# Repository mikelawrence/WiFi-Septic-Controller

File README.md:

# Wireless Septic Controller
I had some problems with my newly installed aerobic septic system when hurricane Harvey blew through. There was no significant flooding but there was plenty of rain and that seemed to cause the system to override pump multiple times. This board is designed to give visibility as to how often the pump runs and will detail alarm conditions. The effluent pump is controlled with an external 50A Solid-State-Relay (SSR). This board also provides an alarm output required by most aerobic septic systems. Normally the alarm switches are wired in parallel so that any alarm condition will turn on the light and audible alert. This board has separate inputs for three alarm switches so that the alarm condition can be identified. This board supports the following alarm types: air pressure failure alarm, tank high level alarm, and bleach low level alarm. WiFi is provided by an ATWINC1500 module which is an excellent low power WiFi module that is directly supported by Arduino. This board is fully compatible with the Arduino MRK1000 which includes a SAMD21G18 ARM processor and a ATWINC1500 module. This board uses MQTT to communicate with Home Assistant home automation software. The MQTT client/server model is very effective in this situation.

This PCB design uses my custom libraries available here [Mike's KiCad Libraries](https://github.com/mikelawrence/KiCad-Libraries).

This PCB was designed with [KiCad 5.1.2](http://kicad.org).

_Note: There is dangerous voltage present on this PCB. Use care when handling this board. Housing this board in a box is required to protect users from electrocution._

_Note: The LMZ21700 Simple Switcher, SAMD21G18 ARM Processor, and ATWINC1500 WiFi Module have exposed pads on the bottom which requires either a reflow oven or hot air to solder properly._

For Bill of Materials generation I use my version of [KiBoM](https://github.com/mikelawrence/KiBoM) forked from [SchrodingersGat](https://github.com/SchrodingersGat/KiBoM).

## Status
* Rev 1.1 PCB has been updated to support KiCad 5.1 libraries. Some footprints changed when libraries were updated but changes were minimal. This board has NOT been tested.
  * Order the PCB from [OSH Park](https://oshpark.com/shared_projects/a805S6zq).
  * Order the parts from Mouser using this [Shared BOM](https://www.mouser.com/ProjectManager/ProjectDetail.aspx?AccessID=a71ed4612f).
* Rev 1.0 PCB has been ordered, assembled, and tested. Hardware is fully operational.
  * Order the PCB from [OSH Park](https://oshpark.com/shared_projects/bguWSc9J).
  * Order the parts from Mouser using this [Shared BOM](https://www.mouser.com/ProjectManager/ProjectDetail.aspx?AccessID=a71ed4612f).

## Board Preview

## Design
### Input Power
A transformer converts the 115VAC to 10VAC through a standard bridge rectifier and capacitor filter to arrive at approximately 12VDC. This voltage is fed to both a 3.3VDC and 5VDC Simpler Switcher from Texas Instruments (LMZ21700). The switchers can also be fed by the 5VDC from the USB connector when the 115VAC is not connected. But make note, the 5VDC is no longer regulated.

### Alarm Contact Inputs
There are three alarm contact inputs: air pressure failure alarm, tank high level alarm, and bleach low level alarm. Aerobic septic systems have an air compressor that pumps air into the septic tank, hence the name "aerobic". This air pump promotes bacterial growth and it runs all the time. If the air pump stops producing air pressure the air pressure failure alarm contact closes. Many aerobic septic systems use liquid bleach for the chlorine source and some regulatory boards require a low bleach level alarm. My aerobic septic system has three float switches but only one is the tank high level alarm. This float switch is at the highest point in the tank and this alarm means the pump cannot keep up with the water entering the tank. This is usually caused by the effluent pump failing.

In the previous wiring of the septic controller the alarm contacts were wired in parallel logically "or'ing" the alarms. The contacts switched 115VAC to the alarm light and audible alert. In order to determine the actual alarm state the wiring was changed to directly connect these contacts to the the board and they no longer switch 115VAC. The alarm contact inputs use a simple pullup to 5VDC and a Schmidt Trigger Inverter (SN74LVC2G14). Note: software debounce is still required. A high value pullup resistor and series resistor (both 100k) were selected to reduce current levels when accidental high voltages are applied to the input. ESD Protection devices are included to further protect the inputs. Due the inverted nature of the SN74LVC2G14 the software sees a logic high when the contact is closed.

### Sense Inputs
There are two 115VAC sense inputs (S1 and S2). These inputs are connected to an On Semiconductor MID400 AC Line Monitor. This optically-isolated device provides a logic low when 115VAC is present on the input. There is no flickering due to 60Hz AC. S1 is used to sense when the effluent pump has power. These is needed because the effluent pump can be turned on when the override float is tripped. S2 is currently unused.

### Relay Outputs
There are two relay outputs on the PR and ALM. Both are switched 115VAC by small board mount solid state relays  (). These SSRs provide overload protection for both temperature and current. The Pump Relay (PR) output is connected to the effluent pump 50A solid state relay (Crydom CWA2450-10). A 50A relay is needed to drive the 3/4hp effluent pump. Note this relay is controlled by 115VAC. The other relay output (AL) is the alarm output. The alarm light and audible alert require 10W at 115VAC. The alarm output is switched on when any alarm contact is closed. There is no software intervention required to produce an alarm.

### SAMD ARM Processor and WiFi Module
The ARM processor and ATWINC1500 WiFi module are wired identical to the MKR1000 Arduino board, thus the Arduino development environment is used for software development and the ATWINC1500 module is directly supported. Digital power is 3.3V and while the LCD is 5V there are no 5V outputs driving 3.3V inputs on the ARM processor so there is no problem wiring the LCD directly to the ARM processor. The LCD recognizes anything above 2.2VDC as a high so 3.3VDC logic outputs from ARM processor will be correctly interpreted by the LCD.

## Setup
### Arduino Setup
This board is designed to mimic a [MKR1000](https://store.arduino.cc/usa/arduino-mkr1000) board from Arduino. Make sure the the MKR1000 board is supported by installing Arduino SAMD Boards package. Do this by opening the Board Manager as shown below.

Type in "samd" in the filter edit and you will see several options. Select "Arduino SAMD Boards (32-bits ARM Cortex-M0+)" and install the latest version as shown below.

It will take a few minutes to download and install the board package. Once complete it's time to install the necessary libraries. Start by opening the Library Manager as shown below.

Type in "mqtt" in the filter edit and scroll down until you see "MQTT by Joel Gaehwiler" as shown below.

Once "MQTT" is installed repeat the install for the following libraries.

* WiFi101 by Arduino
* WiFiOTA by Arduino
* OneWire by Paul Stoffregen and many others
* DallasTemperature by Miles Burton and others

### Board Setup
The Arduino development environment expects a bootloader in the SAMD ARM processor which will allow programming via USB. The bootloader must be programmed first using a supported programming pod. I used an "Atmel-ICE" pod but there are other options. First make sure you have selected the "Arduino/Genuino MKR1000" board as shown below.

Next select your programmer.

Make sure the board is powered via USB and the programmer is connected to the debug connector then select "Burn Bootloader".

Now the bootloader is programmed it's time to load the "WiFi101 FirmwareUpdater" example. This will update the firmware in the ATWINC1500 module.

Now "Upload" the "WiFi101 FirmwareUpdater" example.

Update the ATWINC1500 module by selecting "WiFi101 Firmware Updater".

Click the "Update Firmware" button.

Finally open the "Septic_WiFi_Controller.ino" sketch downloaded from GitHub. Update the necessary defines for your Wireless network and MQTT server settings see the [Code README](code/README.md) for more information. Now upload it just like the "WiFi101 FirmwareUpdater" example. All done!

# Acknowledgments
[Arduino](www.arduino.cc) kindly develops open source hardware and software which makes writing software for the board incredibly easy.

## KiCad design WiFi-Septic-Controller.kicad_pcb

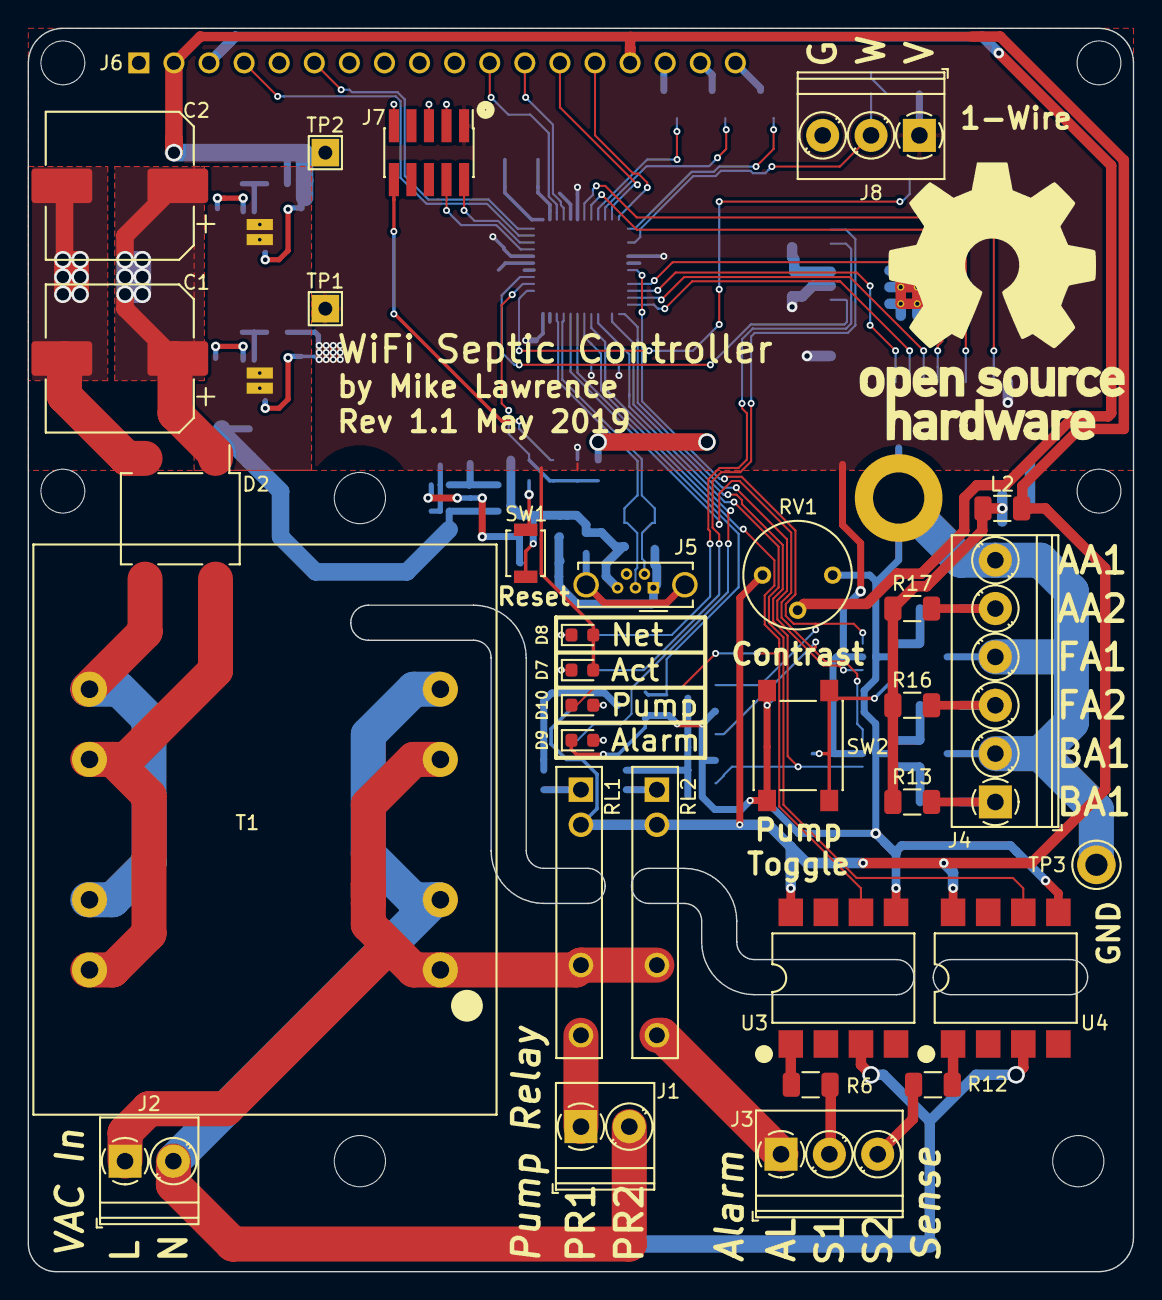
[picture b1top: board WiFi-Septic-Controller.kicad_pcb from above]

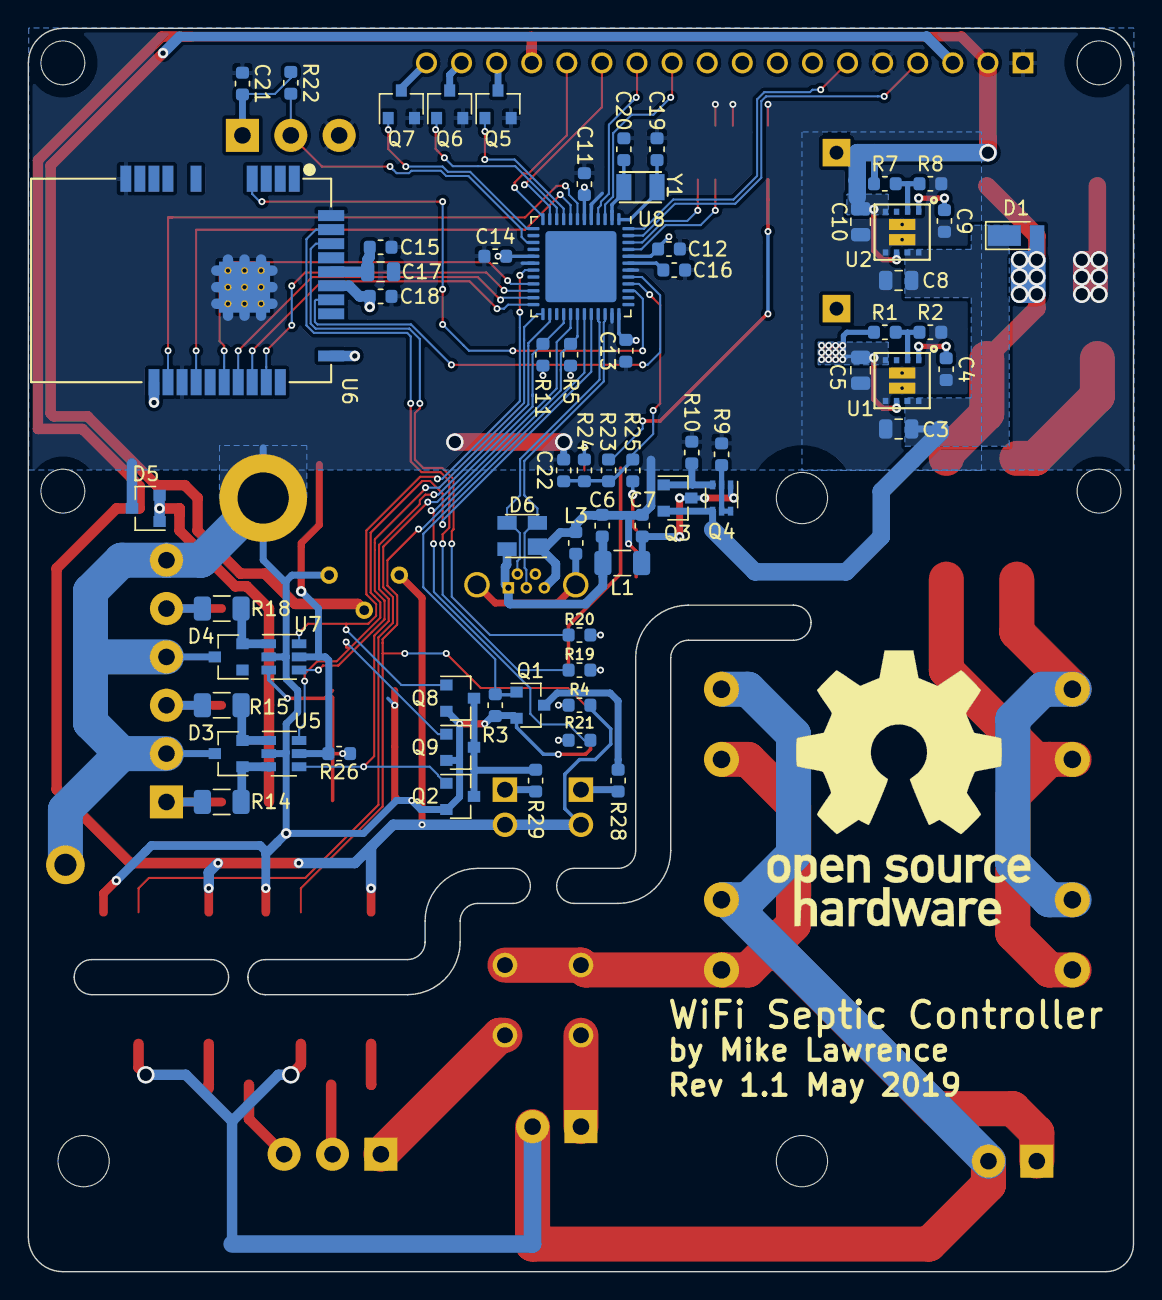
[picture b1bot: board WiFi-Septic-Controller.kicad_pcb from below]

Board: 2 copper layers, 80.0 x 90.0 mm, 102 parts (66 on the bottom side), 83 nets.

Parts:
C1, C2: 330uF; CP_Elec_10x10.5
C3, C5, C8, C10, C17: 22uF; C_0805_2012Metric
C4, C9: 3300pF; C_0603_1608Metric
C6, C7: 1000pF; C_0603_1608Metric
C11, C12, C13, C14, C15, C21, C22: 0.1uF; C_0603_1608Metric
C16, C18: 1uF; C_0603_1608Metric
C19, C20: 15pF; C_0603_1608Metric
D1: DFLS130; D_PowerDI-123
D2: D_Bridge_+-AA; Diode_Bridge_Vishay_DFS
D3, D4, D5: TPD2E2U06; SOT-23
D6: PRTR5V0U2X; SOT-143
D7: Yellow; LED_0603_1608Metric
D8: Green; LED_0603_1608Metric
D9: Red; LED_0603_1608Metric
D10: Blue; LED_0603_1608Metric
J1, J2: Screw_Terminal_01x02; TerminalBlock_Phoenix_PT-1,5-2-3.5-H_1x02_P3.50mm_Horizontal
J3, J8: Screw_Terminal_01x03; TerminalBlock_Phoenix_PT-1,5-3-3.5-H_1x03_P3.50mm_Horizontal
J4: Screw_Terminal_01x06; TerminalBlock_Phoenix_PT-1,5-6-3.5-H_1x06_P3.50mm_Horizontal
J5: USB_B_Micro; USB_Micro-B_Wuerth_614105150721_Vertical_CircularHoles
J6: GWT-C1627A-RGB
J7: Cortex Debug; PinHeader_2x05_P1.27mm_Vertical_SMD
L1, L2: 1k@100MHz; L_1206_3216Metric
L3: 470@100MHz; L_0603_1608Metric
MK1: Mounting_Hole_PAD; 6-32_PTH_Mounting_Hole
MK2, MK3, MK4: 6-32_NPTH_Mounting_Hole
Q1, Q2, Q5, Q6, Q7, Q8, Q9: 2N7002; SOT-23
Q3: DMG2305UX; SOT-23
Q4: BCM857BS; SOT-363_SC-70-6
R1: 1.21M; R_0603_1608Metric
R2: 383k; R_0603_1608Metric
R3, R5, R9, R11, R24, R26: 10k; R_0603_1608Metric
R4: 169R; R_0603_1608Metric
R6, R12, R13, R14, R15, R16, R17, R18: 22k; R_1206_3216Metric
R7: 232k; R_0603_1608Metric
R8: 44.2k; R_0603_1608Metric
R10: 47k; R_0603_1608Metric
R19, R20, R21: 130R; R_0603_1608Metric
R22: 4.7k; R_0603_1608Metric
R23: 39R; R_0603_1608Metric
R25: 330R; R_0603_1608Metric
R28, R29: 698R; R_0603_1608Metric
RL1, RL2: CPC1511Y; Relay_IXYS_PowerSIP
RV1: 10k; Potentiometer_Bourns_3339P_Vertical
SW1: Reset; SW_SPST_B3U-1000P
SW2: Pump; SW_SPST_PTS645
T1: VPP-XFMR; Triad_VPP_5.0VA
TP1: 3.3V; TestPoint_THTPad_2.0x2.0mm_Drill1.0mm
TP2: 5V; TestPoint_THTPad_2.0x2.0mm_Drill1.0mm
TP3: GND; TestPoint_Keystone_5010-5014_Multipurpose
U1, U2: LMZ21700; Converter_DCDC_Texas-SIL0008E
U3, U4: MID400; SMDIP-8_W9.53mm
U5, U7: 74LVC2G14; SOT-23-6
U6: ATWINC1500-MR210UB; Microchip_ATWINC1500-MR210UB
U8: SAMD21G18-M; QFN-48-1EP_7x7mm_P0.5mm_EP5.15x5.15mm
Y1: 32.768kHz; Crystal_SMD_Abracon_ABS07-2Pin_3.2x1.5mm

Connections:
+3V3: C5.1, C11.2, C12.2, C13.2, C14.2, C18.2, C21.2, D7.2, D8.2, J7.1, J8.1, R1.1, R5.2, R11.2, R22.1, R24.2, R26.1, TP1.1, U1.4, U1.6, U5.5, U6.10, U6.20, U6.23, U7.5, U8.6, U8.17, U8.36, U8.44
+5V: C10.1, J6.2, J6.15, L2.1, R4.2, R7.1, RL1.2, RL2.2, RV1.3, TP2.1, U2.4, U2.6, U3.8, U4.8
+12V: C1.1, C2.1, D1.2, D2.1
/A0: J6.11, U8.3
/A1: J6.4, U8.47
/A2: J6.6, U8.48
/A3: Q5.1, U8.9
/A4: Q6.1, U8.10
/A5: J6.13, U8.11
/A6: J6.14, U8.12
/ALM: J3.1, RL2.4
/AREF: J6.12, U8.4
/D0: Q1.1, R3.1, U8.31
/D1: Q9.1, U5.6, U8.32
/D2: J8.2, R22.2, U8.15
/D4: Q8.1, U7.6, U8.19
/D6: R21.1, U8.29
/D7: D10.1, R5.1, U3.6, U8.30
/MISO: R11.1, U4.6, U8.28
/MOSI: U7.4, U8.25
/P1: J3.2, R6.1
/P2: J3.3, R12.1
/PR1: J1.1, RL1.4
/SCK: Q2.1, U5.4, U8.26
/SDA: Q7.1, U8.13
/SWCLK: J7.4, U8.45
/SWDIO: J7.2, U8.46
/USB_N: D6.3, J5.2, U8.33
/USB_P: D6.2, J5.3, U8.34
/VSUPPLY: C3.1, C8.1, D1.1, Q3.2, Q4.4, U1.7, U1.8, U2.7, U2.8
/WINC_EN: U6.22, U8.41
/WINC_MISO: U6.17, U8.24
/WINC_MOSI: U6.15, U8.21
/WINC_SCK: U6.18, U8.22
/WINC_WAKE: U6.11, U8.7
/~RESET~: C22.2, R23.1, R24.1, R25.1, U8.40
/~WINC_IRQ: U6.13, U8.8
/~WINC_RST: U6.4, U8.39
/~WINC_SS: U6.16, U8.23
GND: C1.2, C2.2, C3.2, C4.2, C5.2, C6.1, C7.1, C8.2, C9.2, C10.2, C11.1, C12.1, C13.1, C14.1, C15.1, C16.1, C17.2, C18.1, C19.1, C20.1, C21.1, C22.1, D2.2, D3.3, D4.3, D5.3, D6.1, D9.1, J4.2, J4.4, J4.6, J5.5, J6.1, J6.5, J7.3, J7.5, J7.9, J8.3, L3.1, MK1.1, Q1.2, Q2.2, Q5.2, Q6.2, Q7.2, Q8.2, Q9.2, R2.2, R3.2, R8.2, R9.2, R10.2, RV1.1, SW1.2, SW2.2, TP3.1, U1.5, U1.9, U1.10, U2.5, U2.9, U2.10, U3.5, U4.5, U5.2, U6.9, U6.12, U6.28, U6.29, U7.2, U8.5, U8.18, U8.35, U8.42
LINE: J2.1, RL1.3, RL2.3, T1.1, T1.4
NEUT: J1.2, J2.2, T1.3, T1.6, U3.3, U4.3
unnamed: C4.1, U1.1
unnamed: C7.2, L1.2, Q3.3, Q4.1
unnamed: C9.1, U2.1
unnamed: C15.2, C17.1, U6.24
unnamed: C16.2, U8.43
unnamed: C19.2, U8.1, Y1.1
unnamed: C20.2, U8.2, Y1.2
unnamed: D2.3, T1.9, T1.12
unnamed: D2.4, T1.7, T1.10
unnamed: D3.1, R14.2, U5.3
unnamed: D3.2, R15.2, U5.1
unnamed: D4.2, R18.2, U7.1
unnamed: D5.1, D5.2, L2.2, R13.1, R16.1, R17.1
unnamed: D7.1, R19.2
unnamed: D8.1, R20.2
unnamed: D9.2, R21.2
unnamed: D10.2, R4.1
unnamed: J4.1, R13.2, R14.1
unnamed: J4.3, R15.1, R16.2
unnamed: J4.5, R17.2, R18.1
unnamed: J5.6, L3.2
unnamed: J6.3, RV1.2
unnamed: J6.16, Q5.3
unnamed: J6.17, Q6.3
unnamed: J6.18, Q7.3
unnamed: J7.10, R23.2
unnamed: Q1.3, R28.1
unnamed: Q2.3, Q8.3, Q9.3, R29.1
unnamed: Q3.1, Q4.3, R10.1
unnamed: Q4.2, Q4.5, Q4.6, R9.1
unnamed: R1.2, R2.1, U1.2
unnamed: R6.2, U3.1
unnamed: R7.2, R8.1, U2.2
unnamed: R12.2, U4.1
unnamed: R19.1, U6.27
unnamed: R20.1, U6.26
unnamed: R25.2, SW1.1
unnamed: R26.2, SW2.1, U7.3
unnamed: R28.2, RL1.1
unnamed: R29.2, RL2.1
VBUS: C6.2, D6.4, J5.1, L1.1

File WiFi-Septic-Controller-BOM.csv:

Quantity,References,Description,Manufacturer,Part Number,Vendor,Vendor Part Number
2,C1 C2,"CAP, SMD 10X10.5, 20%, EC, 50V",Panasonic,EEE-FT1H331GP,Mouser,667-EEE-FT1H331GP
5,C3 C5 C8 C10 C17,"CAP, 0805, 22uf, 20%, X5R, 25V",Taiyo Yuden,TMK212BBJ226MG-TT,Mouser,963-TMK212BBJ226MGTT
2,C4 C9,"CAP, 0603, 3300pF, 5%, X7R, 10V",Vishay,VJ0603Y332JXQPW1BC,Mouser,77-VJ0603Y332JXQPBC
2,C6 C7,"CAP, 0603, 1000pF, 10%, X7R, 10V",Vishay,VJ0603Y102KXAAC31,Mouser,77-VJ0603Y102KXAAC31
7,C11 C12 C13 C14 C15 C21 C22,"CAP, 0603, 0.1uF, 20%, X7R, 10V",Vishay,VJ0603Y104JXQPW1BC,Mouser,77-VJ0603Y104JXQPBC
2,C16 C18,"CAP, 0603, 1uF, 20%, X7R, 10V",TDK,CGB3B1X7R1A105M055AC,Mouser,810-CGB3B1X7R1A105MC
2,C19 C20,"CAP, 0603, 15pF, 5%, C0G, 50V",AVX,06035A150JAT2A,Mouser,581-06035A150J
1,D1,"DIO, PowerDI123, Schottky Rectifier, 30V, 1A",Diodes Inc,DFLS130LQ,Mouser,621-DFLS130L
1,D2,"DIO, DFS, Bridge Diode, 2A, 600V",Comchip Tech,DF206ST-G,Mouser,750-DF206ST-G
3,D3 D4 D5,"TVS, SOT23, ESD TVS Protection, Dual",Texas Instruments,TPD2E2U06QDBZRQ1,Mouser,595-TPD2E2U06QDBZRQ1
1,D6,"TVS, SOT23, ESD Protection, USB",Nexperia,"PRTR5V0U2X,215",Mouser,771-PRTR5V0U2X-T/R
1,D7,"LED, 0603, Yellow LED",Lumex,SML-LX0603SYW-TR,Mouser,696-SML-LX0603SYW
1,D8,"LED, 0603, Green LED",Lumex,696-SMLLX0603SGWTR,Mouser,696-SML-LX0603SGW
1,D9,"LED, 0603, Red LED",Lumex,SML-LX0603SRW-TR,Mouser,696-SML-LX0603SRW
1,D10,"LED, 0603, Blue LED",Lumex,SML-LX0603USBW-TR,Mouser,696-SML-0603USBWTR
2,J1 J2,"CON, THT, Terminal Block, 3.5mm, 2 Pos",Phoenix Contact,1984617,Mouser,651-1984617
2,J3 J8,"CON, THT, Terminal Block, 3.5mm, 3 Pos",Phoenix Contact,1984620,Mouser,651-1984620
1,J4,"CON, THT, Terminal Block, 3.5mm, 6 Pos",Phoenix Contact,1984659,Mouser,651-1984659
1,J5,"CON, THT, Micro USB 2.0 Type AB, Vertical",Wurth Electronics,614105150721,Mouser,710-614105150621
1,J6,"CON, THT, 2.54mm Socket, Single Row, Vertical, 18 Pos",Samtec,SSW-150-01-G-S,Digikey,SAM1209-50-ND
1,J7,"CON, SMD, 1.27mm Header, Dual Row, Vertical, 10 Pos",Amphenol FCI,202112100010C4LF,Mouser,649-202112100010C4LF
2,L1 L2,"BEAD, 1206, 1k@100MHz, 2A",Murata,BLM31KN102SH1L,Mouser,81-BLM31KN102SH1L
1,L3,"BEAD, 0603, 470R@100MHz, 1A",Murata,BLM18PG471SN1D,Mouser,81-BLM18PG471SN1D
7,Q1 Q2 Q5 Q6 Q7 Q8 Q9,"TRANS, SOT23, Mosfet, P-CH, 115mA, 60V",On Semiconductor,2N7002L,Mouser,512-2N7002L
1,Q3,"TRANS, SOT23, Mosfet, P-CH, -5A, -20V",Diodes Inc,DMG2305UX-7,Mouser,621-DMG2305UX-7
1,Q4,"TRANS, SOT363, Bipolar, PNP, Dual Matched",Diodes Inc,BCM857BS-7-F,Mouser,621-BCM857BS-7-F
1,R1,"RES, 0603, 1.21M, 1%, T100",Yageo,RC0603FR-071M21L,Mouser,603-RC0603FR-071M21L
1,R2,"RES, 0603, 383k, 1%, T100",Panasonic,ERJ-3EKF3833V,Mouser,667-ERJ-3EKF3833V
6,R3 R5 R9 R11 R24 R26,"RES, 0603, 10k, 1%, T100",Panasonic,ERJ-3EKF1002V,Mouser,667-ERJ-3EKF1002V
1,R4,"RES, 0603, 169R, 1%, T100",Panasonic,ERJ-3EKF1690V,Mouser,667-ERJ-3EKF1690V
8,R6 R12 R13 R14 R15 R16 R17 R18,"RES, 1206, 22k, 5%, T200",Panasonic,ERJ-P08J223V,Mouser,667-ERJ-P08J223V
1,R7,"RES, 0603, 232k, 1%, T100",Yageo,RC0603FR-07232KL,Mouser,603-RC0603FR-07232KL
1,R8,"RES, 0603, 44.2k, 1%, T100",Panasonic,ERJ-3EKF4422V,Mouser,667-ERJ-3EKF4422V
1,R10,"RES, 0603, 47k, 1%, T100",Panasonic,ERJ-3EKF4702V,Mouser,667-ERJ-3EKF4702V
3,R19 R20 R21,"RES, 0603, 130R, 1%, T100",Panasonic,ERJ-3EKF1300V,Mouser,667-ERJ-3EKF1300V
1,R22,"RES, 0603, 4.7k, 1%, T100",Panasonic,ERJ-3EKF4701V,Mouser,667-ERJ-3EKF4701V
1,R23,"RES, 0603, 39R, 1%, T100",Panasonic,ERJ-3EKF39R0V,Mouser,667-ERJ-3EKF39R0V
1,R25,"RES, 0603, 330R, 1%, T100",Panasonic,ERJ-3EKF3300V,Mouser,667-ERJ-3EKF3300V
2,R28 R29,"RES, 0603, 698R, 1%, T100",Panasonic,ERJ-3EKF6980V,Mouser,667-ERJ-3EKF6980V
2,RL1 RL2,"RLY, THT, Solid State, Form A, Protected, 230V, 450mA",IXYS,CPC1511Y,Mouser,849-CPC1511
1,RV1,"POT, THT, 10k, Round",Bourns,3339P-1-103LF,Mouser,652-3339P-1-103LF
1,SW1,"SW, SMD, Push Button",Omron,B3U-1000P,Mouser,653-B3U-1000P
1,SW2,"SW, SMD, Push Button",Panasonic,PTS645SK70SMTR92LFS,Mouser,611-PTS645SM13SMTR92
1,T1,"XFMR, THT, 120/240V to 8/16V, 310mA",Triad Magnetics,VPP16-310,Mouser,553-VPP16-310
2,U1 U2,"MODULE, SMD, Simple Switcher, 17V, .65A",TI,LMZ21700SILR,Mouser,595-LMZ21700SILR
2,U3 U4,"IC, SMDIP8, Optical AC Line Monitor",On Semi,MID400S,Mouser,512-MID400S
2,U5 U7,"IC, SOT23-6, Dual inverting Schmitt trigger",Texas Instruments,SN74LVC2G14DBVG4,Mouser,595-SN74LVC2G14DBVG4
1,U6,"MODULE, SMD, WiFi, u.FL connector",Atmel,ATWINC1500-MR210UB1140,Mouser,579-C1500MR210UB1140
1,U8,"IC, QFN44, MCU, ARM, 256kB Flash, 32kB SRAM, 48MHz",Atmel,ATSAMD21G18A-MUT,Mouser,556-ATSAMD21G18A-MUT
1,Y1,"XTL, SMD, 32.768kHz",Abracon,ABS07-32.768KHZ-9-T,Mouser,815-ABS07-32.768K9T





Component Groups:,50
Component Count:,95
Fitted Components:,95
Number of PCBs:,1
Total components:,95
Schematic Version:,1.1
Schematic Date:,May 2019
BoM Date:,"Wednesday, May 15, 2019 at 09:08:21 PM"
Schematic Source:,/Users/mike/Documents/KiCad/WiFi-Septic-Controller/WiFi-Septic-Controller.sch
KiCad Version:,Eeschema (5.1.2-1)-1

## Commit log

2018-05-14 Initial commit. Board sent out for fab. No code yet.
2018-05-14 Fix README errors and add missing images.
2018-05-14 Update 3D board preview.
2018-05-14 Update 3D board view again.
2018-05-14 Changed ALM label on schematic to match PCB silkscreen.
2018-05-15 Chnage file names to be more consistent.
2018-05-15 Removed relative link to pdfs that don't work.
2018-05-17 Updated 3D Model. Minor README corrections.
2018-05-21 Changed transformer part number. Alarm Labels on schematic now match PCB positions. Update PCB Status.
2018-05-21 Added wiring diagram.
2018-05-22 First commit of the Arduino Sketch.
2018-05-27 First operational version. Software now working in actual system.
    First operation software version. Added Septic Wiring Diagram (use draw.io). Added Arduino's RCTZero directly to project to add getTime() which greatly improves time read perfomance.
2018-05-27 Minor README corrections.
2018-05-31 Upped Version to 0.2. Added over temperature for SSR. Watchdog Timeout changed.
    Solid State Relay will now be disabled when temperature exceeds 65C. Temperature no longer has a faster publish rate when the pump is on, instead Temperature and RSSI publish every minute. Watchdog T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
2018-06-03 Disabled "Reset MQTT Connect" status. Fixed temperature publishing catchup.
    Status no longer sends a "Reset MQTT Connect" status. Fixed temperature publishing to prevent a series of catchup publishes if the MQTT server was offline for a while.
2018-06-11 Upped version to 0.3. Improved WiFi reliablity, add NTP handling.
    Sometime WIFi looses access to network without showing disconnected in status. To get around this timeout on MQTT connect retries was added. This stops the WiFi connection so it can reconnect. The AT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
2018-06-11 Fix time not updating properly.
2018-06-12 Added automatic support for testing on other boards.
    Minor corrections in README.
2018-07-05 Increase alarm input debounce time.
    Occasionally seeing High Float Alarms around the time the pump turns off.
2018-07-08 Change alarm input resistors
    The 100k alarm input resistors may be a high enough impedance to allow noise to trigger the over full alarm. Changed the resistors to 22k. Minor update to README file.
2018-07-23 Update to KiCad 5.0.0. Remove unecessary files.
2018-08-21 Update Status in README.
    Also updated KiCad libraries.
2018-11-28 Update libraries and cleanup.
    Update WiFi101 library to 0.15.3. WIFI_CONNECTION_RETRY_TIME changed to 15 minutes (increase from 5 minutes). Cleanup comments. Version to 0.4.
2019-03-03 Arduino IDE 1.8.8,updated WINC1500 firmware to 19.6.1, updated MQTT to 2.4.1.
2019-03-12 Fix Watchdog Timer reset when NTP server fails to respond.
    Doubled the Watchdog timer reset period to 128 seconds to prevent reset when NTP server takes too long to respond on power cycle. Small cleanup to comments and commented code.
2019-05-05 Update to KiCad 5.1 libraries.
    Also updated custom libraries.
2019-05-05 Edit README
2019-05-11 Remove unnecessary gerbers. Update gerber generation settings.
2019-05-16 Cleanup BOM. VCC now +3V3.
    Add KiBoM support.
    Cleanup part information in schematic.
    Added power pins to schematic on multi-unit gates.
2019-05-21 Arduino library updates.
2019-06-05 Minor formatting cleanup.
2019-06-29 Add Home Assistant availability topic to all nodes.
2019-07-02 Add "device_class" to Alarm Config.
2019-12-09 Update library and Arduino IDE version.
2021-03-28 Add Home Assistant device support
    This will now show up as a device under mqtt integration. All entities will be associated with the device. Unique_id comes from SAMD21 processor serial.
2021-04-04 New device branch
    Breakout MQTT options into separate calls.
    Change ntp server/
2021-04-04 Revert to more stable code
    Recent changes to add Home Assistant device information to the MQTT topics caused instability. This is probably related to String library usage. The changes that caused problems are now in the device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
2021-04-04 Change MQTT options
    Switch NTP server to time.nist.gov
2021-11-08 Update Kicad link.
